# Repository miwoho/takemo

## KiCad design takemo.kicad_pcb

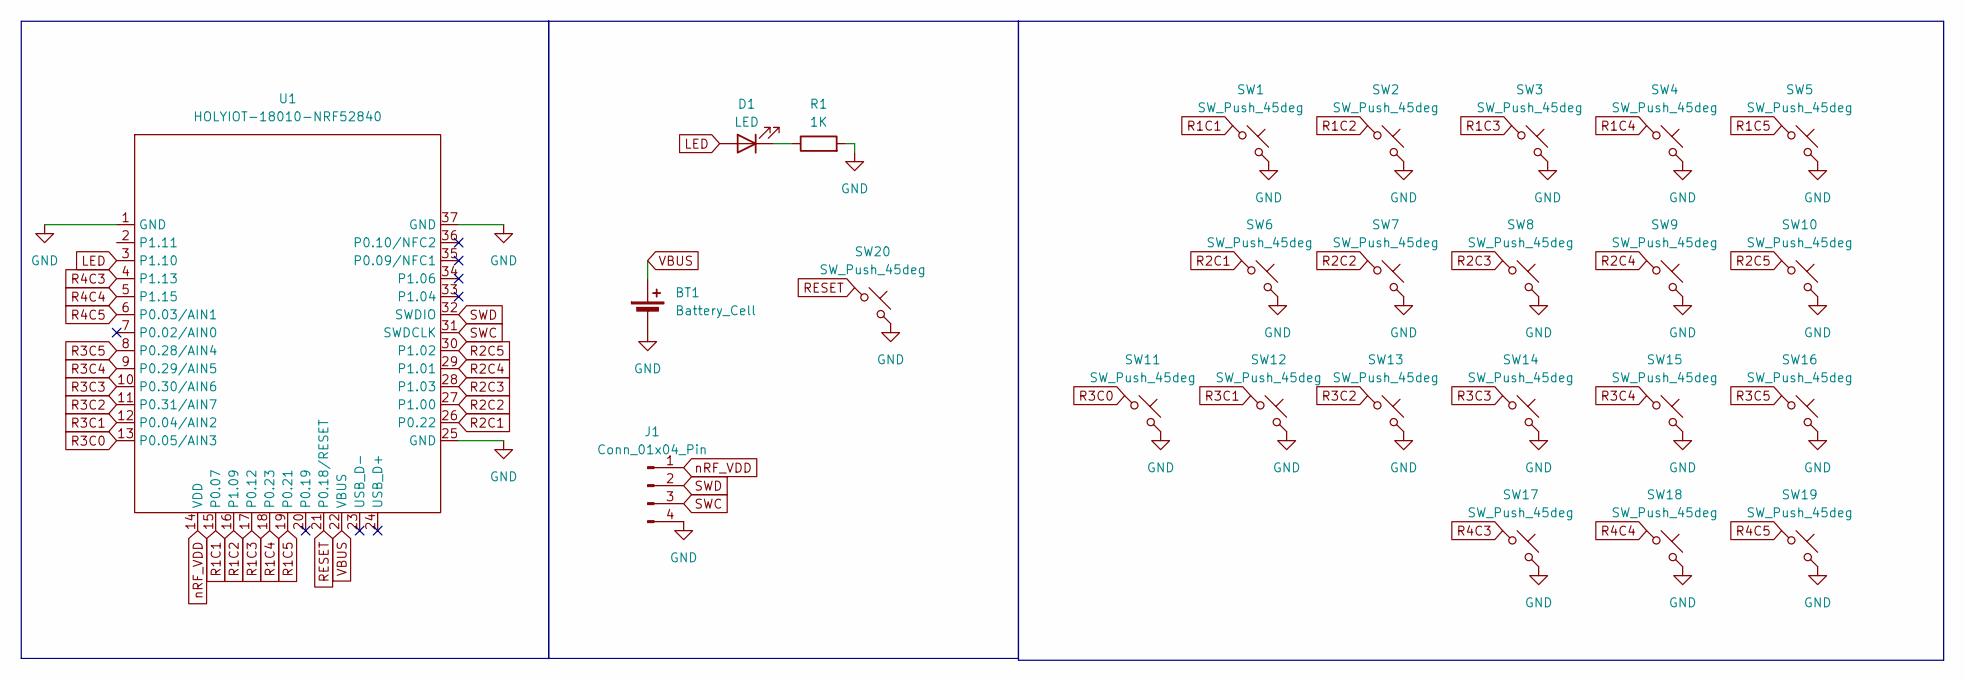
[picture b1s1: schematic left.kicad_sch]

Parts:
BT1: Battery_Cell; BAT-SMD_MY-1632-03
D1: LED; LED_0402_1005Metric_Pad0.77x0.64mm_HandSolder
J1: Conn_01x04_Pin; PinHeader_1x04_P1.00mm_Vertical
R1: 1K; R_0402_1005Metric_Pad0.72x0.64mm_HandSolder
SW1, SW2, SW3, SW4, SW5, SW6, SW7, SW8, SW9, SW10, SW11, SW12, SW13, SW14, SW15, SW16, SW17, SW18, SW19: SW_Push_45deg; CPG1316S01D02
SW20: SW_Push_45deg; SW_SPST_B3U-3000P-B
U1: HOLYIOT-18010-NRF52840; Holyiot-18010-nRF52840

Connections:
GND: BT1.2 (-), J1.4, R1.2, SW1.2, SW2.2, SW3.2, SW4.2, SW5.2, SW6.2, SW7.2, SW8.2, SW9.2, SW10.2, SW11.2, SW12.2, SW13.2, SW14.2, SW15.2, SW16.2, SW17.2, SW18.2, SW19.2, SW20.2, U1.1 (GND), U1.25 (GND), U1.37 (GND)
LED: D1.2 (A), U1.3 (P1.10)
unnamed: D1.1 (K), R1.1
R1C1: SW1.1, U1.15 (P0.07)
R1C2: SW2.1, U1.16 (P1.09)
R1C3: SW3.1, U1.17 (P0.12)
R1C4: SW4.1, U1.18 (P0.23)
R1C5: SW5.1, U1.19 (P0.21)
R2C1: SW6.1, U1.26 (P0.22)
R2C2: SW7.1, U1.27 (P1.00)
R2C3: SW8.1, U1.28 (P1.03)
R2C4: SW9.1, U1.29 (P1.01)
R2C5: SW10.1, U1.30 (P1.02)
R3C0: SW11.1, U1.13 (P0.05/AIN3)
R3C1: SW12.1, U1.12 (P0.04/AIN2)
R3C2: SW13.1, U1.11 (P0.31/AIN7)
R3C3: SW14.1, U1.10 (P0.30/AIN6)
R3C4: SW15.1, U1.9 (P0.29/AIN5)
R3C5: SW16.1, U1.8 (P0.28/AIN4)
R4C3: SW17.1, U1.4 (P1.13)
R4C4: SW18.1, U1.5 (P1.15)
R4C5: SW19.1, U1.6 (P0.03/AIN1)
RESET: SW20.1, U1.21 (P0.18/RESET)
SWC: J1.3, U1.31 (SWDCLK)
SWD: J1.2, U1.32 (SWDIO)
VBUS: BT1.1 (+), U1.22 (VBUS)
nRF_VDD: J1.1, U1.14 (VDD)

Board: 2 copper layers, 25 parts (0 on the bottom side), 27 nets, no tracks yet.

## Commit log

2025-11-16 upload left sch
2025-11-16 add README.md
2025-11-16 add .gitignore
2025-11-18 add step
